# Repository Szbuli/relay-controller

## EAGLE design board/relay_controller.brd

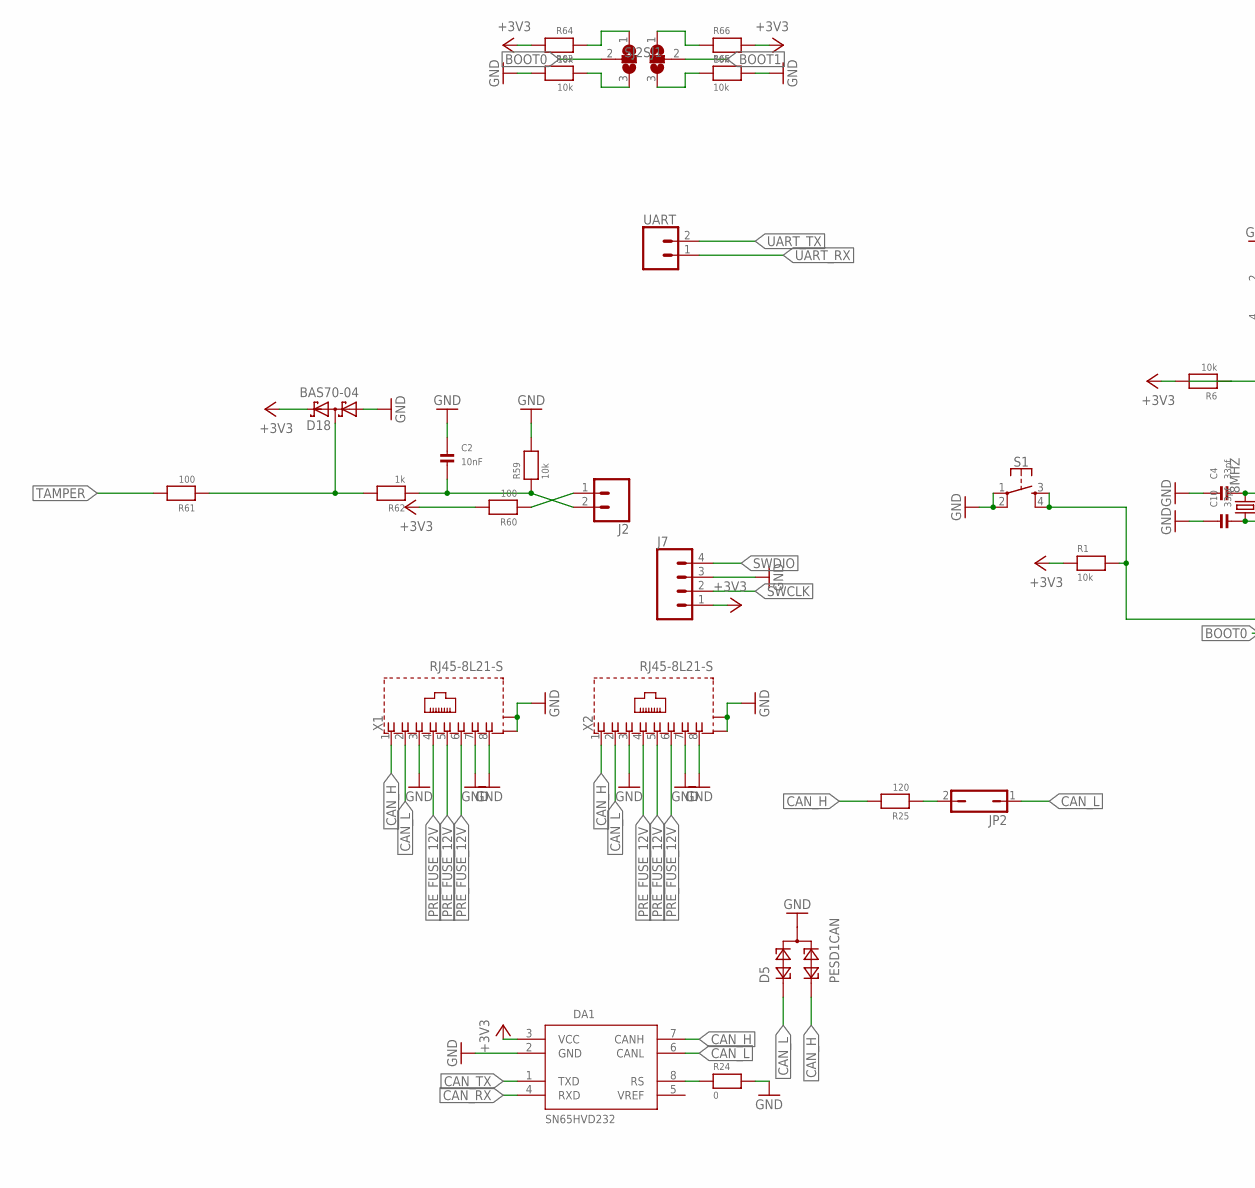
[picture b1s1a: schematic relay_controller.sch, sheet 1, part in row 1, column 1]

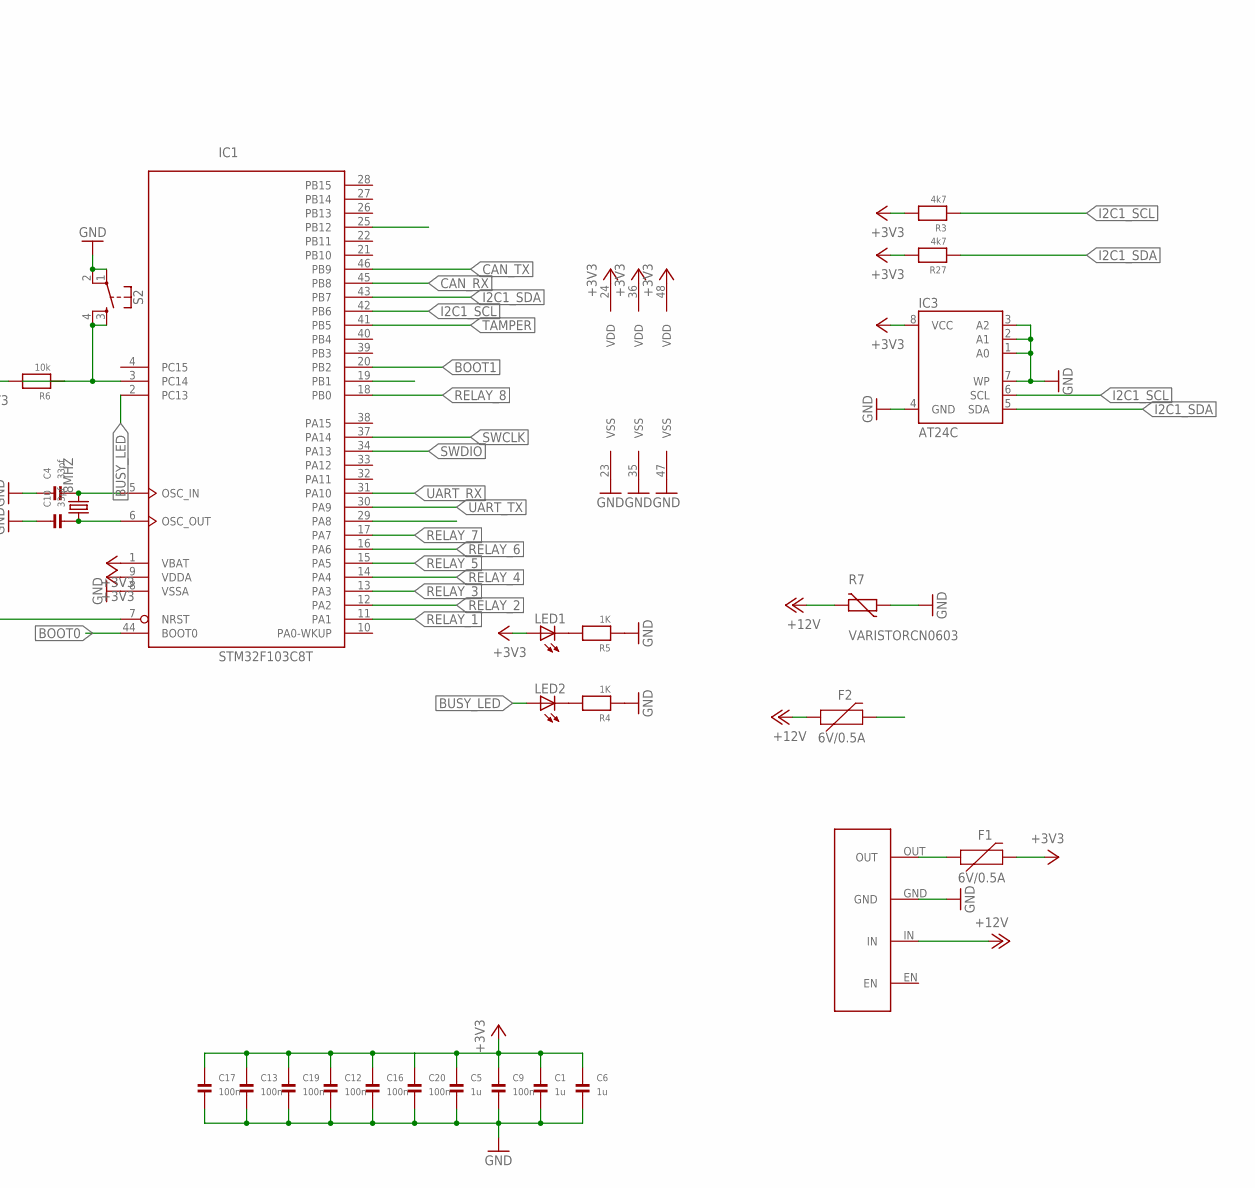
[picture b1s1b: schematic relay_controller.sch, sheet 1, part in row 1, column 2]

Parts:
8MHZ: CRYSTALHC49UP; HC49UP
C1, C5, C6: 1u; 0603
C2: 10nF; 0603
C4, C10: 33pf; 0603
C9, C12, C13, C16, C17, C19, C20: 100n; 0603
D5: PESD1CAN; SOT23
D18: BAS70-04; SOT23
DA1: SN65HVD232; SO08
F1, F2: 6V/0.5A; 1206
IC1: STM32F103C8T; LQFP48
IC3: AT24C; SOIC8
J2: CONN_023.5MM; SCREWTERMINAL-3.5MM-2
J7: CONN_04POLAR_LOCK; MOLEX-1X4_LOCK
JP2: JP1Q; JP1
LED1, LED2: LEDCHIPLED_0805; CHIPLED_0805
R1, R6, R59, R63, R64, R65, R66: 10k; 0603
R3, R27: 4k7; 0603
R4, R5: 1K; 0603
R7: VARISTORCN0603; CT/CN0603
R24: 0; 0603
R25: 120; 0603
R60, R61: 100; 0603
R62: 1k; 0603
S1, S2: MOMENTARY-SWITCH-SPST-2-SMD-4.6X2.8MM; TACTILE_SWITCH_SMD_4.6X2.8MM
SJ1, SJ2: SJ2W; SJ_2
U$1: HW-613
UART: CONN_02; 1X02
X1, X2: RJ45-8L21-S; RJ45-SHIELD1

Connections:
+3V3: C1.1, C5.1, C6.1, C9.1, C12.1, C13.1, C16.1, C17.1, C19.1, C20.1, D18.2 (C2), DA1.3 (VCC), F1.2, IC1.1 (VBAT), IC1.9 (VDDA), IC1.24 (VDD), IC1.36 (VDD), IC1.48 (VDD), IC3.8 (VCC), J7.1, LED1.A, R1.1, R3.2, R6.2, R27.2, R60.2, R64.2, R66.2
+12V: F2.1, R7.2, U$1.IN; also elsewhere on the board
ASDASD: D18.3 (C1A2), R61.1, R62.2
BOOT0: IC1.44 (BOOT0), SJ1.2
BOOT1: IC1.20 (PB2), SJ2.2
BUSY_LED: IC1.2 (PC13), LED2.A
CAN_H: D5.2, DA1.7 (CANH), R25.2, X1.1, X2.1
CAN_L: D5.1, DA1.6 (CANL), JP2.1, X1.2, X2.2
CAN_RX: DA1.4 (RXD), IC1.45 (PB8)
CAN_TX: DA1.1 (TXD), IC1.46 (PB9)
GND: C1.2, C2.1, C4.1, C5.2, C6.2, C9.2, C10.1, C12.2, C13.2, C16.2, C17.2, C19.2, C20.2, D5.3, D18.1 (A1), DA1.2 (GND), IC1.8 (VSSA), IC1.23 (VSS), IC1.35 (VSS), IC1.47 (VSS), IC3.1 (A0), IC3.2 (A1), IC3.3 (A2), IC3.4 (GND), IC3.7 (WP), J7.3, R4.1, R5.1, R7.1, R24.2, R59.2, R63.2, R65.2, S1.1, S1.2, S2.1, S2.2, U$1.GND, X1.3, X1.7, X1.8, X1.S1 (S), X1.S2 (S), X2.3, X2.7, X2.8, X2.S1 (S), X2.S2 (S); also elsewhere on the board
I2C1_SCL: IC1.42 (PB6), IC3.6 (SCL), R3.1
I2C1_SDA: IC1.43 (PB7), IC3.5 (SDA), R27.1
unnamed: 8MHZ.2, C4.2, IC1.5 (OSC_IN)
unnamed: 8MHZ.1, C10.2, IC1.6 (OSC_OUT)
unnamed: F1.1, U$1.OUT
unnamed: C2.2, J2.2, R59.1, R62.1
unnamed: LED1.C, R5.2
unnamed: IC1.3 (PC14), R6.1, S2.3, S2.4
unnamed: LED2.C, R4.2
unnamed: J2.1, R60.1
unnamed: IC1.7 (NRST), R1.2, S1.3, S1.4
unnamed: JP2.2, R25.1
unnamed: DA1.8 (RS), R24.1
unnamed: R66.1, SJ2.1
unnamed: R64.1, SJ1.1
unnamed: R65.1, SJ2.3
unnamed: R63.1, SJ1.3
PRE_FUSE_12V: F2.2, X1.4, X1.5, X1.6, X2.4, X2.5, X2.6
RELAY_1: IC1.11 (PA1); also elsewhere on the board
RELAY_2: IC1.12 (PA2); also elsewhere on the board
RELAY_3: IC1.13 (PA3); also elsewhere on the board
RELAY_4: IC1.14 (PA4); also elsewhere on the board
RELAY_5: IC1.15 (PA5); also elsewhere on the board
RELAY_6: IC1.16 (PA6)
RELAY_7: IC1.17 (PA7)
RELAY_8: IC1.18 (PB0)
RELAY_9: IC1.19 (PB1)
RELAY_12: IC1.25 (PB12)
RELAY_16: IC1.29 (PA8)
SWCLK: IC1.37 (PA14), J7.2
SWDIO: IC1.34 (PA13), J7.4
TAMPER: IC1.41 (PB5), R61.2
UART_RX: IC1.31 (PA10), UART.1
UART_TX: IC1.30 (PA9), UART.2

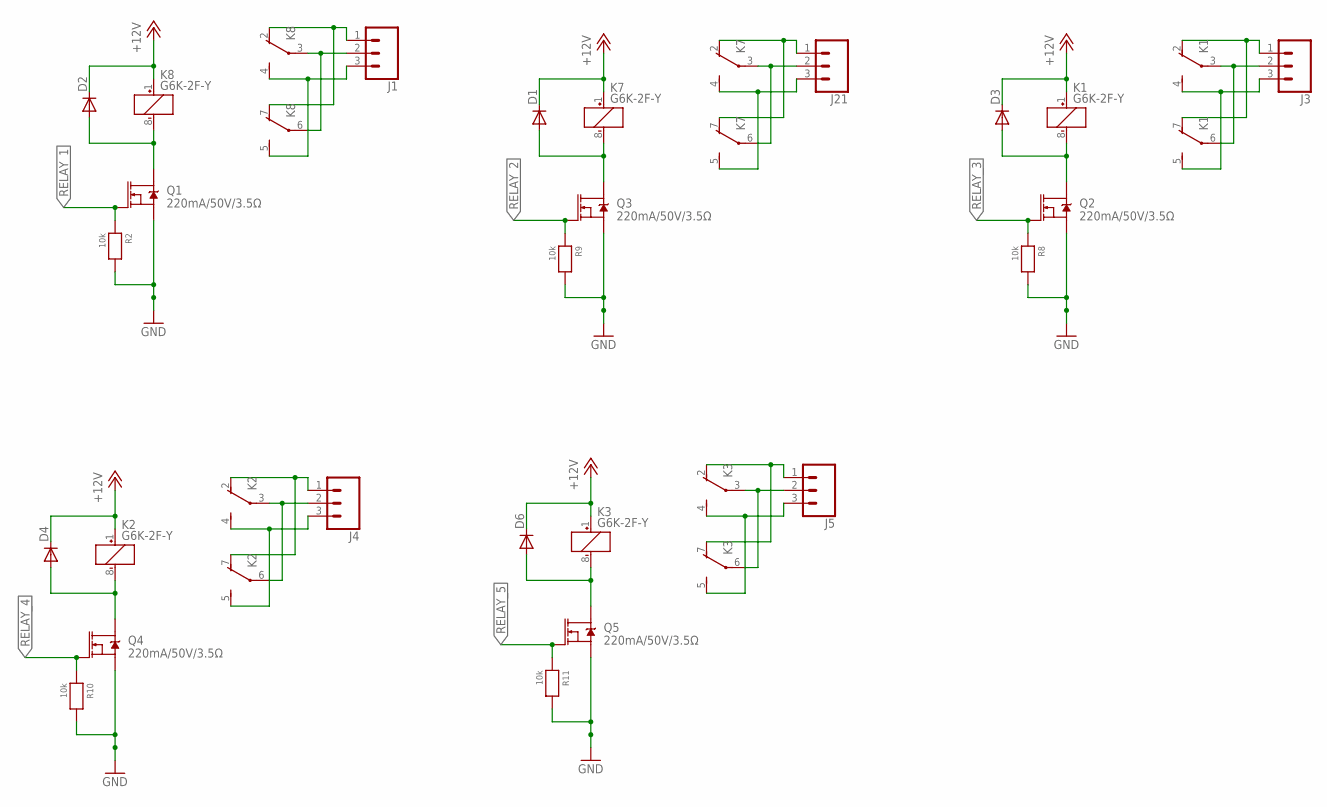
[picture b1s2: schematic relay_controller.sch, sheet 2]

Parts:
D1, D2, D3, D4, D6: DIODE-DO-214AC; DO-214AC
J1, J3, J4, J5, J21: CONN_03SCREW; SCREWTERMINAL-3.5MM-3
K1, K2, K3, K7, K8: G6K-2F-Y
Q1, Q2, Q3, Q4, Q5: 220mA/50V/3.5Ω; SOT23-3
R2, R8, R9, R10, R11: 10k; 0603

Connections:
+12V: D1.C, D2.C, D3.C, D4.C, D6.C, K1.1 (+), K2.1 (+), K3.1 (+), K7.1 (+), K8.1 (+); also elsewhere on the board
GND: Q1.2 (S), Q2.2 (S), Q3.2 (S), Q4.2 (S), Q5.2 (S), R2.2, R8.2, R9.2, R10.2, R11.2; also elsewhere on the board
unnamed: J21.1, K7.2 (O), K7.7 (O)
unnamed: J1.1, K8.2 (O), K8.7 (O)
unnamed: J21.3, K7.4 (S), K7.5 (S)
unnamed: J21.2, K7.3, K7.6
unnamed: D1.A, K7.8 (-), Q3.3 (D)
unnamed: J1.3, K8.4 (S), K8.5 (S)
unnamed: J1.2, K8.3, K8.6
unnamed: D2.A, K8.8 (-), Q1.3 (D)
unnamed: J3.1, K1.2 (O), K1.7 (O)
unnamed: J3.3, K1.4 (S), K1.5 (S)
unnamed: J3.2, K1.3, K1.6
unnamed: D3.A, K1.8 (-), Q2.3 (D)
unnamed: J4.1, K2.2 (O), K2.7 (O)
unnamed: J4.3, K2.4 (S), K2.5 (S)
unnamed: J4.2, K2.3, K2.6
unnamed: D4.A, K2.8 (-), Q4.3 (D)
unnamed: J5.1, K3.2 (O), K3.7 (O)
unnamed: J5.3, K3.4 (S), K3.5 (S)
unnamed: J5.2, K3.3, K3.6
unnamed: D6.A, K3.8 (-), Q5.3 (D)
RELAY_1: Q1.1 (G), R2.1; also elsewhere on the board
RELAY_2: Q3.1 (G), R9.1; also elsewhere on the board
RELAY_3: Q2.1 (G), R8.1; also elsewhere on the board
RELAY_4: Q4.1 (G), R10.1; also elsewhere on the board
RELAY_5: Q5.1 (G), R11.1; also elsewhere on the board

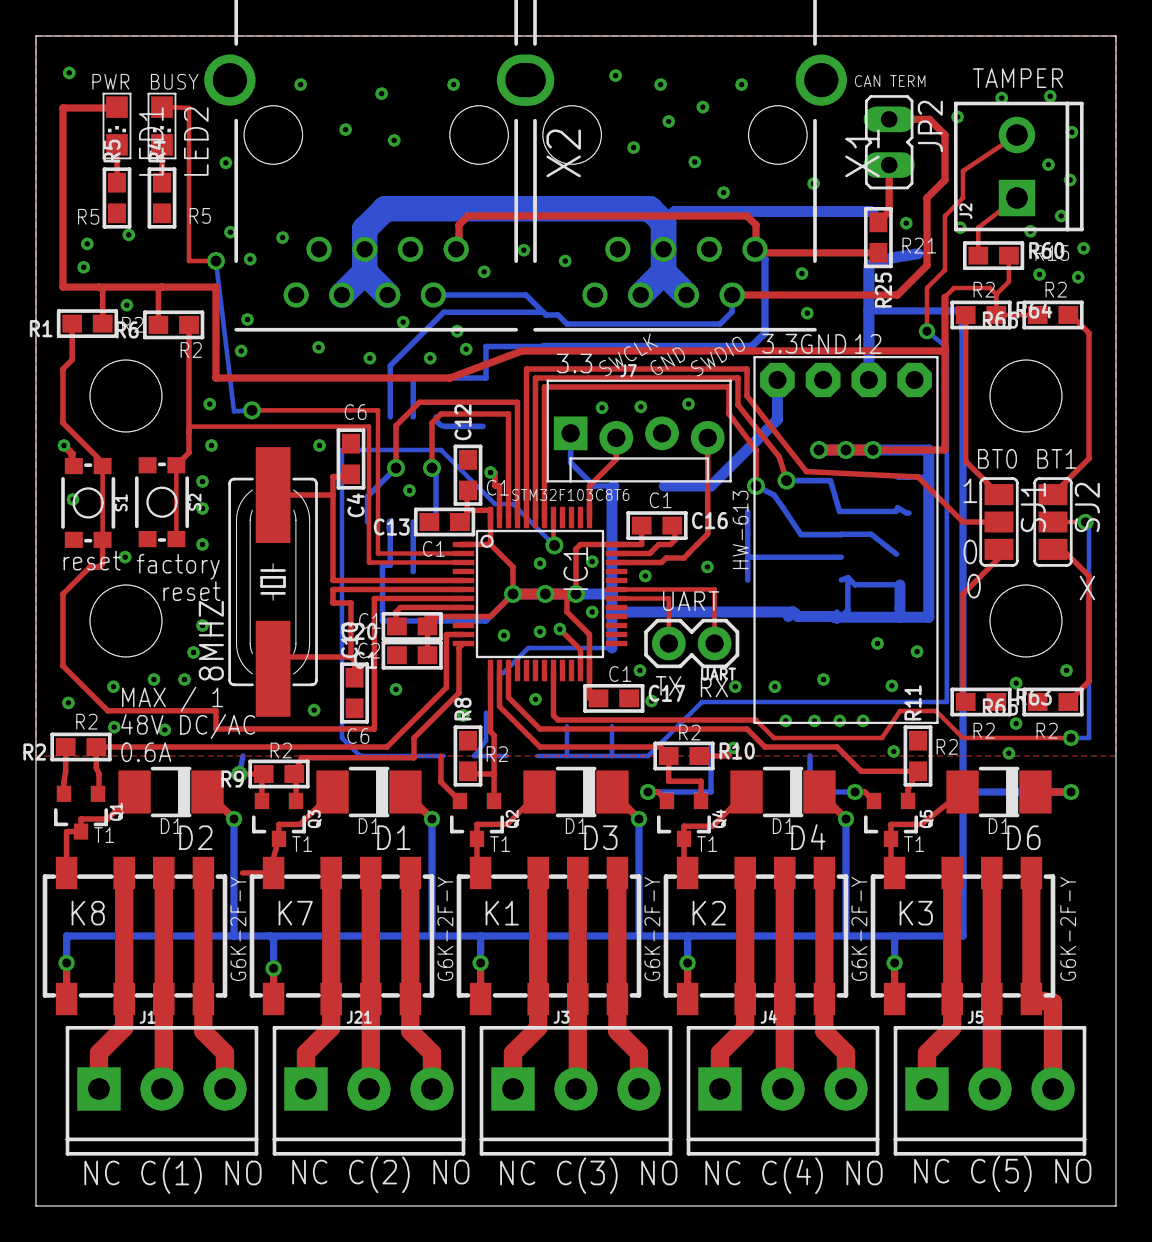
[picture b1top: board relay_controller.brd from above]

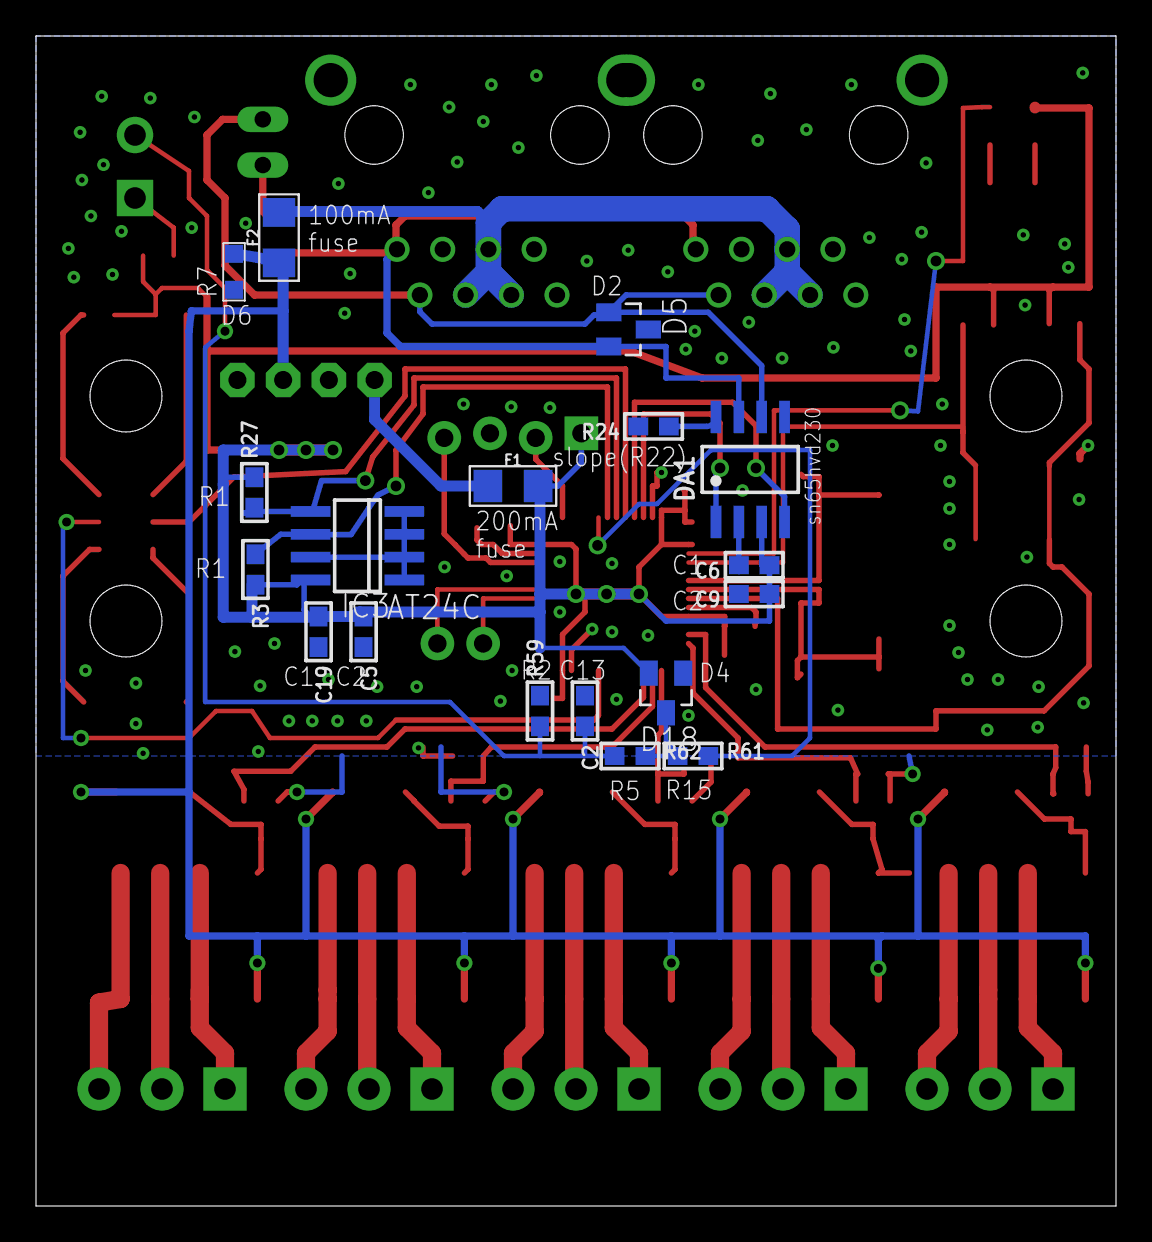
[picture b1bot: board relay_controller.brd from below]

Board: 2 copper layers, 60.0 x 65.0 mm, 78 parts (18 on the bottom side), 59 nets.

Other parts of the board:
U$2, U$3: C45-DIN-MOUNT-2-HOLE-B

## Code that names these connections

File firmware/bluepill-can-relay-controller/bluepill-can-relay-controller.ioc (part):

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Mcu.Name=STM32F103C(8-B)Tx
Mcu.Package=LQFP48
Mcu.UserName=STM32F103C8Tx
PA1.GPIOParameters=PinState,GPIO_Label
PA1.GPIO_Label=RELAY_1
PA1.PinState=GPIO_PIN_RESET
PA1.Signal=GPIO_Output
PA10.Mode=Asynchronous
PA10.Signal=USART1_RX
PA13.Mode=Serial_Wire
PA13.Signal=SYS_JTMS-SWDIO
PA14.Mode=Serial_Wire
PA14.Signal=SYS_JTCK-SWCLK
PA2.GPIOParameters=PinState,GPIO_Label
PA2.GPIO_Label=RELAY_2
PA2.PinState=GPIO_PIN_RESET
PA2.Signal=GPIO_Output
PA3.GPIOParameters=PinState,GPIO_Label
PA3.GPIO_Label=RELAY_3
PA3.PinState=GPIO_PIN_RESET
PA3.Signal=GPIO_Output
PA4.GPIOParameters=PinState,GPIO_Label
PA4.GPIO_Label=RELAY_4
PA4.PinState=GPIO_PIN_RESET
PA4.Signal=GPIO_Output
PA5.GPIOParameters=PinState,GPIO_Label
PA5.GPIO_Label=RELAY_5
PA5.PinState=GPIO_PIN_RESET
PA5.Signal=GPIO_Output
PA9.Mode=Asynchronous
PA9.Signal=USART1_TX
PB5.GPIOParameters=GPIO_Label,GPIO_ModeDefaultEXTI
PB5.GPIO_Label=TAMPER
PB5.GPIO_ModeDefaultEXTI=GPIO_MODE_IT_FALLING
PB5.Signal=GPXTI5
PB6.GPIOParameters=GPIO_Label
PB6.GPIO_Label=I2C_SCL
PB6.Mode=I2C
PB6.Signal=I2C1_SCL
PB7.GPIOParameters=GPIO_Label
PB7.GPIO_Label=I2C_SDA
PB7.Mode=I2C
PB7.Signal=I2C1_SDA
PB8.Mode=CAN_Activate
PB8.Signal=CAN_RX
PB9.Mode=CAN_Activate
PB9.Signal=CAN_TX
PC13-TAMPER-RTC.GPIOParameters=PinState,GPIO_Label
PC13-TAMPER-RTC.GPIO_Label=BUSY_LED
PC13-TAMPER-RTC.PinState=GPIO_PIN_SET
PC13-TAMPER-RTC.Signal=GPIO_Output
PC14-OSC32_IN.GPIOParameters=GPIO_Label
PC14-OSC32_IN.GPIO_Label=FACTORY_RESET
PC14-OSC32_IN.Signal=GPIO_Input
PD0-OSC_IN.Mode=HSE-External-Oscillator
PD0-OSC_IN.Signal=RCC_OSC_IN
PD1-OSC_OUT.Mode=HSE-External-Oscillator
PD1-OSC_OUT.Signal=RCC_OSC_OUT
RCC.SYSCLKFreq_VALUE=72000000
RCC.SYSCLKSource=RCC_SYSCLKSOURCE_PLLCLK
board=bluepill_relay_control

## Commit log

2020-05-06 init relay controller board
2020-05-07 add component labels
2020-05-07 update some labels
2020-05-09 add factory reset button
2020-05-09 add tamper, uart
2020-05-13 init fw
2020-05-13 add init and tamper task
2020-06-06 fix tamper interrupt
2020-06-06 fix hw reset
2020-06-06 fix some labels
2020-06-07 add 3.3v output for relay board
2020-06-07 change default pin state to high
2020-06-10 add 3.3v output
2020-06-12 power over can
2020-06-23 fix config
2020-06-23 add heartbeat
2020-06-29 add varistor
2020-07-01 add current limiting resistor
2020-07-13 refresh libs
2020-07-18 increase size for 5mm inputs
2020-07-18 jumpers for boot mode
2020-07-18 change to solderable boot jumper
2020-07-18 value for current limiting resistor
2020-08-23 update pinout for boot config
2020-08-23 increase heartbeat interval
2020-11-23 change 16 driver pin to 5 relay output (g6k-2f-y)
2020-11-24 DRC check fixes
2020-12-03 add default boot mode label
2021-01-08 fix label
2021-01-08 init migration
2021-01-09 update to new relay
2021-01-09 update header dates
2021-01-09 Cubeide migration (#1)
    * init migration
    * update to new relay
    * update header dates
2021-01-09 init
2021-02-20 init canbus before auto discovery
2021-02-20 fix auto discovery state
2021-02-21 wait on queue when tx mailbox is full
2021-02-28 Feature/ha auto discovery (#2)
    * init
    * init canbus before auto discovery
    * fix auto discovery state
    * wait on queue when tx mailbox is full
2021-02-28 add default value for slope resistor
2021-03-05 update labels
2021-03-07 fix can init order
2021-03-11 more distance between rj45 connectors
2021-03-13 change to packages with place drawing
2021-03-13 remove unused fuse
2021-03-13 change pull down to 10k
2021-03-14 fix labels and place orientation
2021-04-05 fix task init
2021-07-11 heartbeat enabled by default
2021-07-11 add run cfg
2021-07-11 can tx error log
2021-07-11 ignore launch file
2021-08-13 fine tune heartbeat
2021-08-13 trigger heartbeat on first iteration
2021-10-24 add ha status config
2021-10-24 do not send availability topic
2021-10-26 Feature/ha connectivity config (#3)
    * add ha status config
    * do not send availability topic
2021-11-13 add 3.3v to swd connector

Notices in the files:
parts and their libraries:
SparkFun-Connectors: Licensing: Creative Commons ShareAlike 4.0 International - https://creativecommons.org/licenses/by-sa/4.0
microbuilder: This work is placed in the public domain, and may be freely used for commercial and non-commercial work with the following conditions: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
